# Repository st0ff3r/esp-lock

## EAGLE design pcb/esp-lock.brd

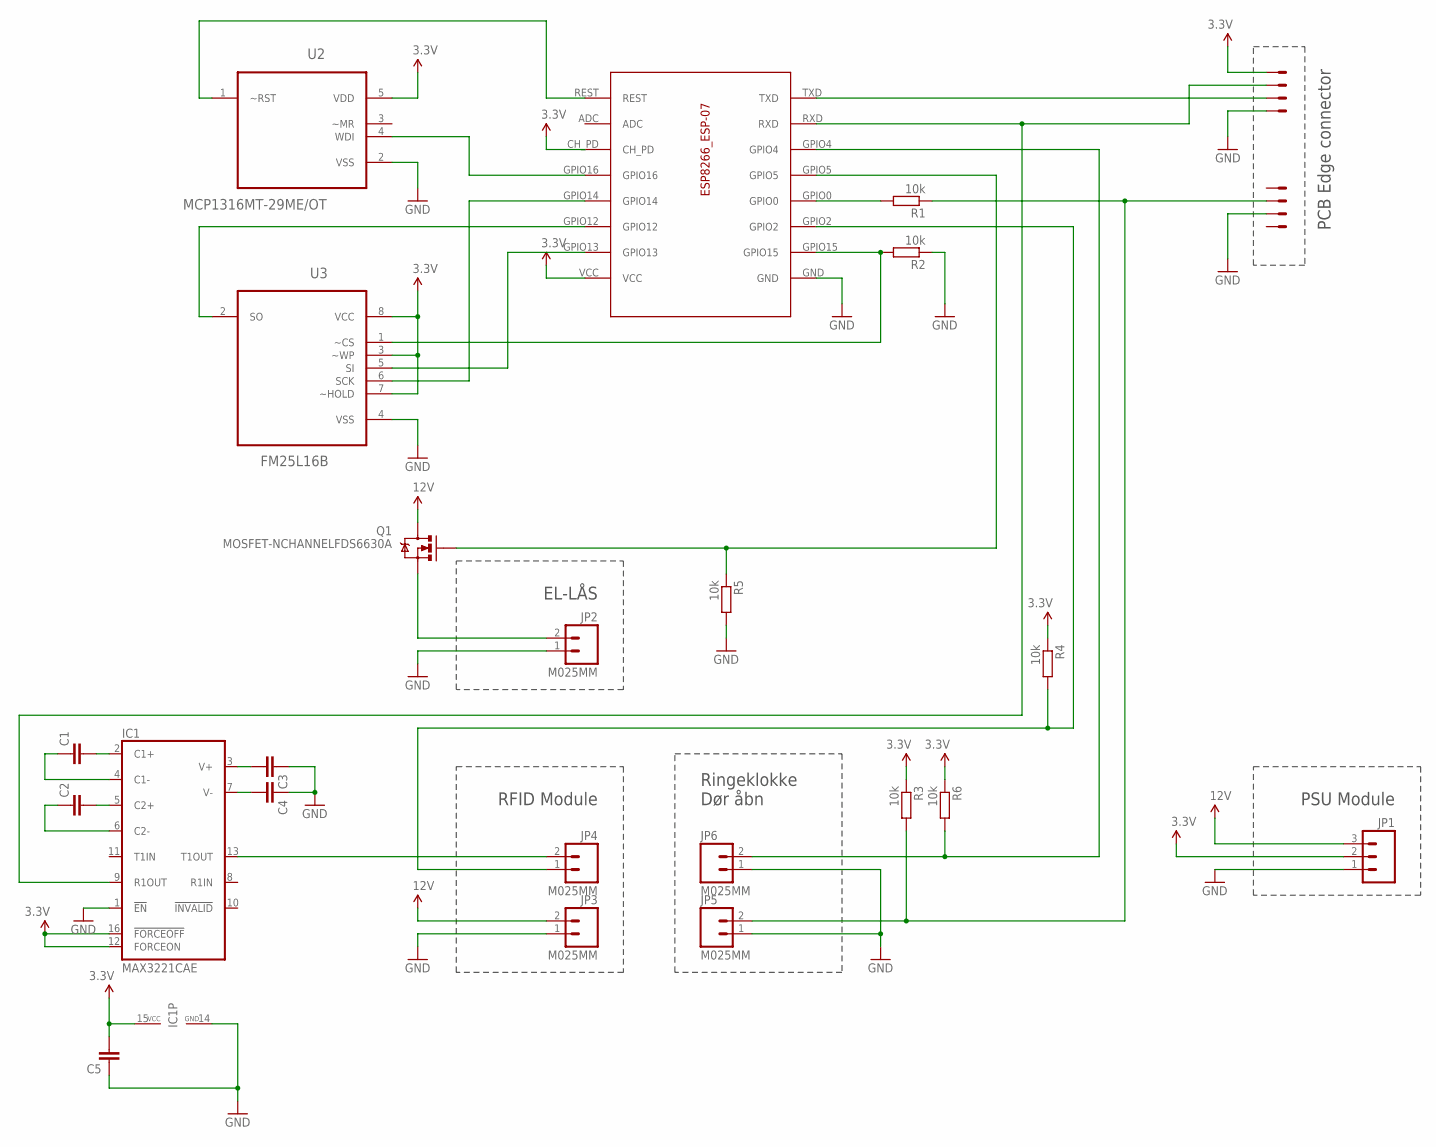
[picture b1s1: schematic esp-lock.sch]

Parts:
C1, C2, C3, C4, C5: CAP0402-CAP; 0402-CAP
ESP8266_ESP-07: ESP8266-07; ESP-07
IC1: MAX3221CAE; SSOP16
JP1: M03-SCREW-5MM; SCREWTERMINAL-5MM-3
JP2, JP3, JP4, JP5, JP6: M025MM; SCREWTERMINAL-5MM-2
Q1: MOSFET-NCHANNELFDS6630A; SO08
R1, R2, R3, R4, R5, R6: 10k; R0805
U2: MCP1316MT-29ME/OT; SOT95P270X145-5N
U3: FM25L16B; SOIC127P600X175-8N
U$1: CON-PCB-SLOT-0.05MINIMAL; CONN_SLOT_MINIMAL

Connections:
3.3V: C5.2, ESP8266_ESP-07.CH_PD, ESP8266_ESP-07.VCC, IC1.12 (FORCEON), IC1.15 (VCC), IC1.16 (!FORCEOFF), JP1.2, R3.1, R4.1, R6.1, U2.5 (VDD), U3.3 (~WP), U3.7 (~HOLD), U3.8 (VCC), U$1.4
5V: JP1.3, JP3.2, Q1.5 (D), Q1.6 (D), Q1.7 (D), Q1.8 (D)
GND: C3.1, C4.1, C5.1, ESP8266_ESP-07.GND, IC1.1 (!EN), IC1.14 (GND), JP1.1, JP2.1, JP3.1, JP5.1, JP6.1, R2.1, R5.2, U2.2 (VSS), U3.4 (VSS), U$1.1, U$1.7
unnamed: ESP8266_ESP-07.TXD, U$1.2
unnamed: ESP8266_ESP-07.RXD, IC1.9 (R1OUT), U$1.3
unnamed: JP2.2, Q1.1 (S), Q1.2 (S), Q1.3 (S)
unnamed: ESP8266_ESP-07.GPIO0, R1.2
unnamed: JP5.2, R1.1, R3.2, U$1.6
unnamed: ESP8266_ESP-07.GPIO2, JP4.1, R4.2
unnamed: ESP8266_ESP-07.GPIO15, R2.2, U3.1 (~CS)
unnamed: ESP8266_ESP-07.REST, U2.1 (~RST)
unnamed: ESP8266_ESP-07.GPIO16, U2.4 (WDI)
unnamed: ESP8266_ESP-07.GPIO12, U3.2 (SO)
unnamed: ESP8266_ESP-07.GPIO5, Q1.4 (G), R5.1
unnamed: ESP8266_ESP-07.GPIO13, U3.5 (SI)
unnamed: ESP8266_ESP-07.GPIO14, U3.6 (SCK)
unnamed: ESP8266_ESP-07.GPIO4, JP6.2, R6.2
unnamed: IC1.13 (T1OUT), JP4.2
unnamed: C4.2, IC1.7 (V-)
unnamed: C3.2, IC1.3 (V+)
unnamed: C1.2, IC1.2 (C1+)
unnamed: C2.2, IC1.5 (C2+)
unnamed: C1.1, IC1.4 (C1-)
unnamed: C2.1, IC1.6 (C2-)

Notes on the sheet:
PSU Module
PCB Edge connector
EL-LÅS
RFID Module
Ringeklokke Dør åbn

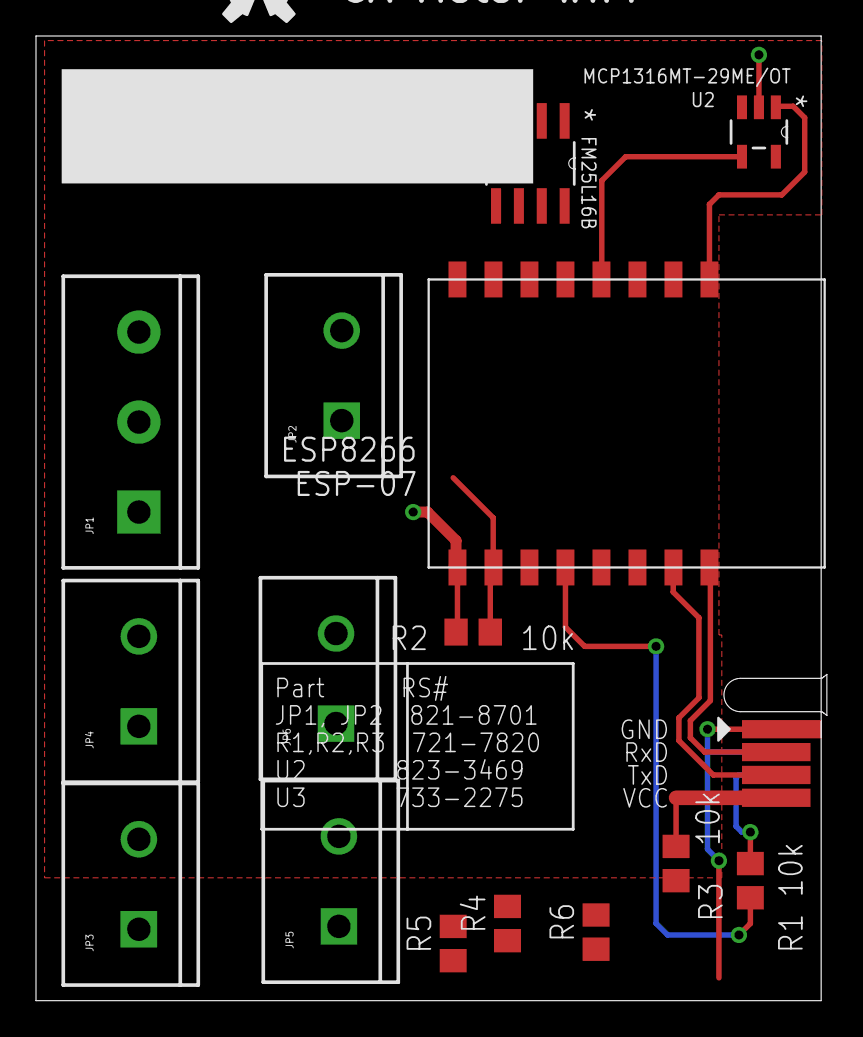
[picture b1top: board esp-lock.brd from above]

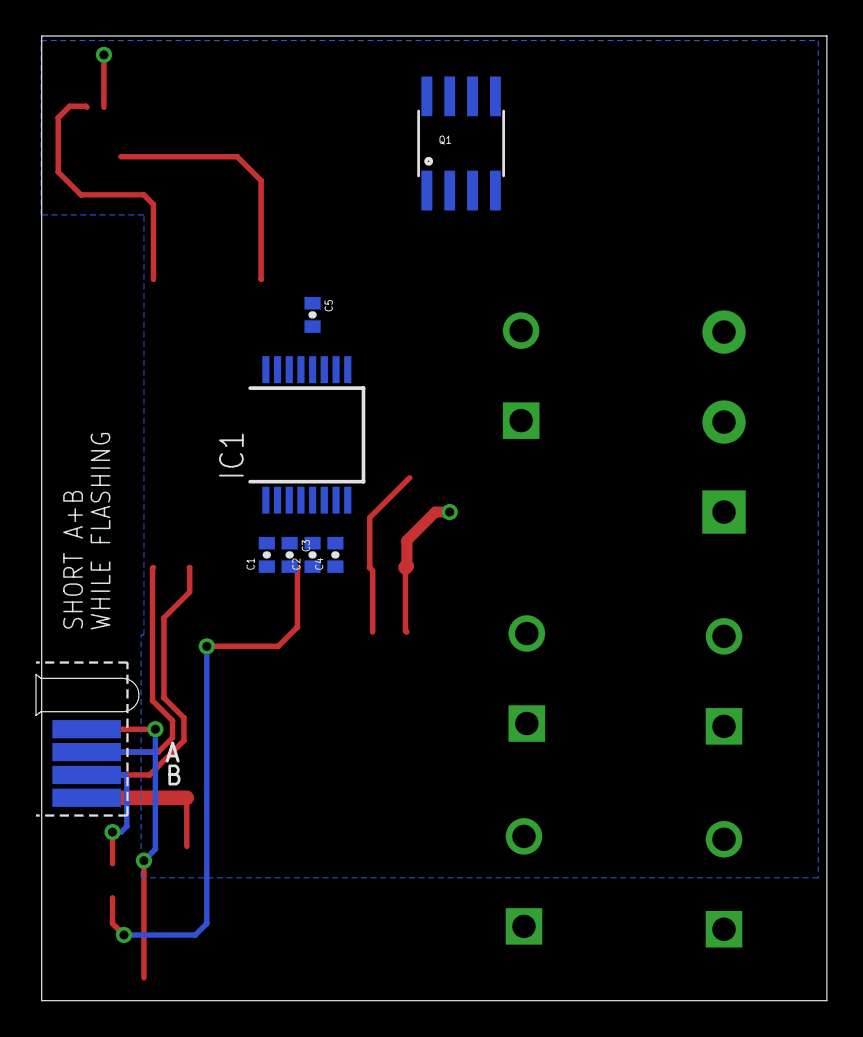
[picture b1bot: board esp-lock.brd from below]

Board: 2 copper layers, 43.6 x 53.6 mm, 24 parts (7 on the bottom side), 24 nets.

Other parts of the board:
U$2: OSHW-LOGO-M

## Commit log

2020-08-25 initial version

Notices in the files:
parts and their libraries:
SparkFun-Connectors: Licensing: CC v3.0 Share-Alike You are welcome to use this library for commercial purposes.
